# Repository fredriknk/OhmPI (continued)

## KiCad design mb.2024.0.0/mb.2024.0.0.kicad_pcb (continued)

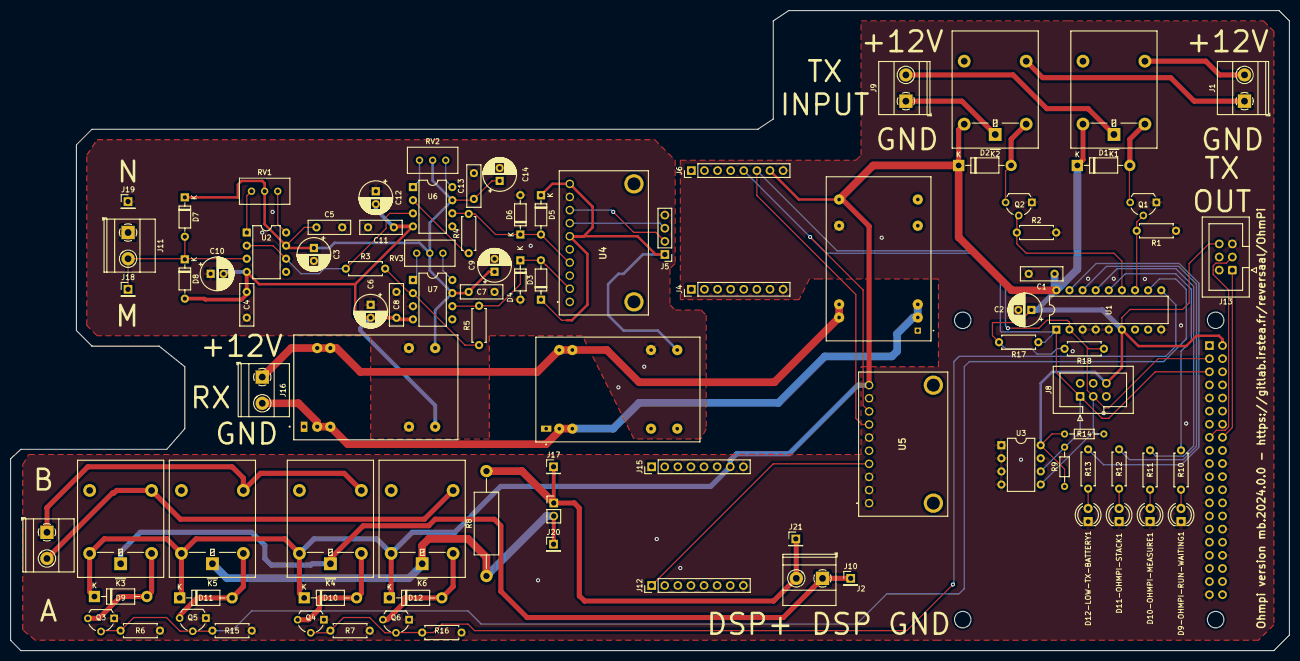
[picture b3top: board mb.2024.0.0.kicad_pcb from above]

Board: 2 copper layers, 247.8 x 124.0 mm, 94 parts (1 on the bottom side), 54 nets.

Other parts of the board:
D7, D8: BAT86; D_DO-35_SOD27_P7.62mm_Horizontal
D9-OHMPI-RUN-WAITING1, D10-OHMPI-MEASURE1, D11-OHMPI-STACK1, D12-LOW-TX-BATTERY1: LED; LED_D4.0mm
R10, R11, R12, R13: 330 ohms; R_Axial_DIN0207_L6.3mm_D2.5mm_P7.62mm_Horizontal

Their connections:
+12V_A: D7.1 (K); also elsewhere on the board
-12V_A: D8.2 (A); also elsewhere on the board
/Vmn_measurement/Electrode_M: D7.2 (A), D8.1 (K); also elsewhere on the board
GNDD: D9-OHMPI-RUN-WAITING1.1 (K), D10-OHMPI-MEASURE1.1 (K), D11-OHMPI-STACK1.1 (K), D12-LOW-TX-BATTERY1.1 (K); also elsewhere on the board
GP4: R10.1; also elsewhere on the board
GP5: R11.1; also elsewhere on the board
GP6: R12.1; also elsewhere on the board
GP7: R13.1; also elsewhere on the board
unnamed: D9-OHMPI-RUN-WAITING1.2 (A), R10.2
unnamed: D10-OHMPI-MEASURE1.2 (A), R11.2
unnamed: D11-OHMPI-STACK1.2 (A), R12.2
unnamed: D12-LOW-TX-BATTERY1.2 (A), R13.2

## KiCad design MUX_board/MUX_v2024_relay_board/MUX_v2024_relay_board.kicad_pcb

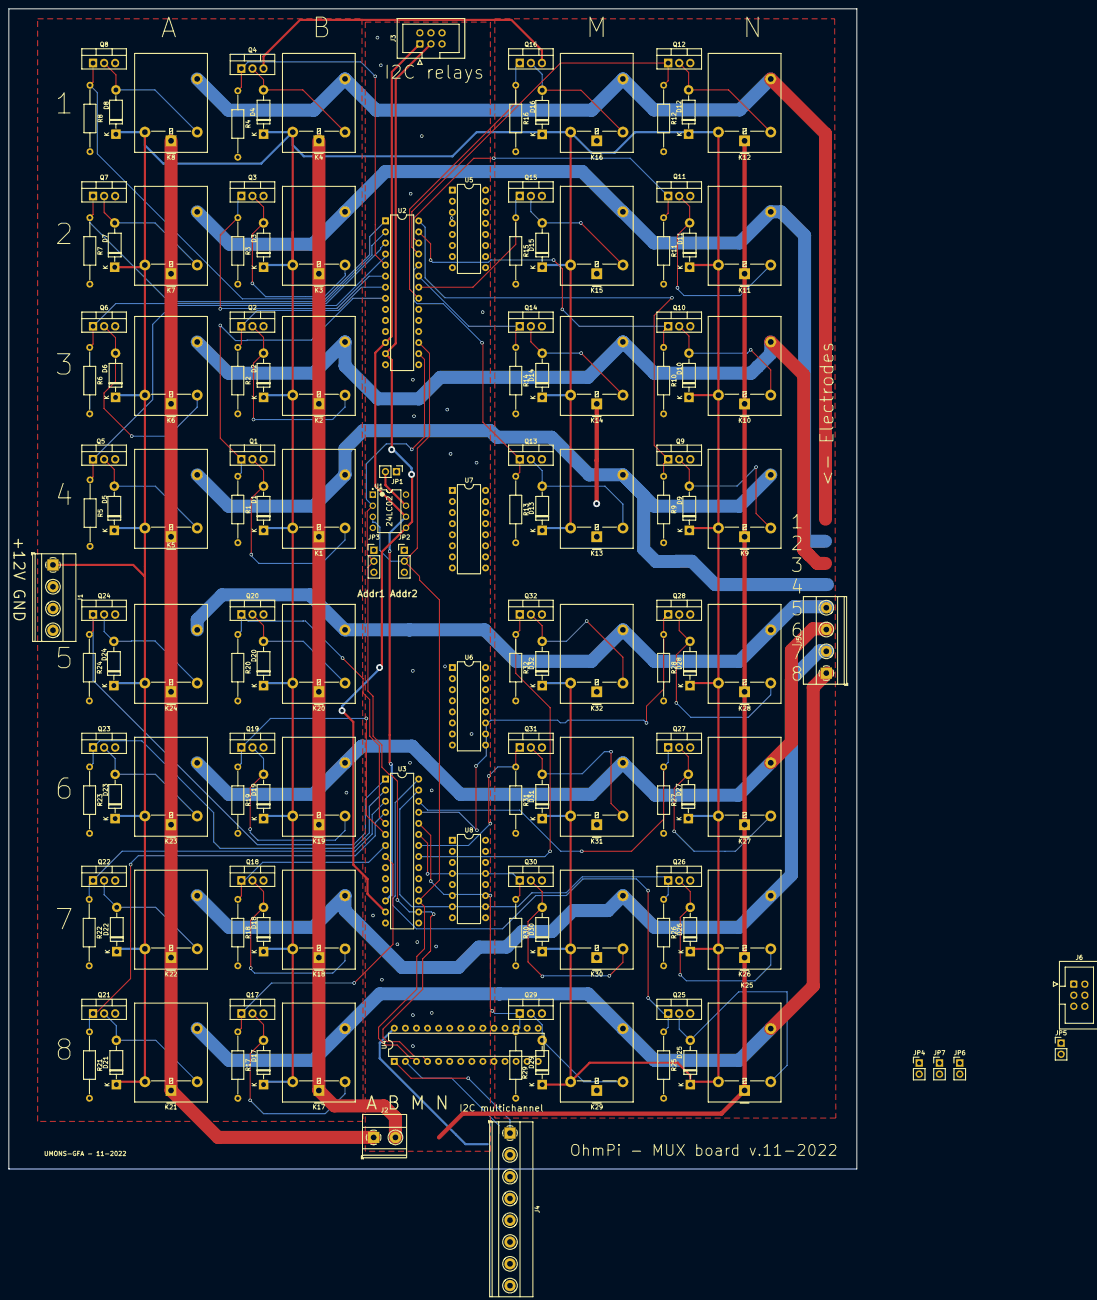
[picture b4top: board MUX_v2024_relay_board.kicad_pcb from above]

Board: 2 copper layers, 194.6 x 266.2 mm, 149 parts (0 on the bottom side), 114 nets.

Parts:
D1, D2, D3, D4, D5, D6, D7, D8, D9, D10, D11, D12, D13, D14, D15, D16, D17, D18, D19, D20, D21, D22, D23, D24, D25, D26, D27, D28, D29, D30, D31, D32: 1N_E4007; D_DO-41_SOD81_P10.16mm_Horizontal
J1, J5: A B M N; TerminalBlock_Phoenix_MKDS-1,5-4_1x04_P5.00mm_Horizontal
J2: Relays Pwr; TerminalBlock_Phoenix_MKDS-1,5-2_1x02_P5.00mm_Horizontal
J3, J6: I2C; IDC-Header_2x03_P2.54mm_Vertical
J4: Screw_Terminal_01x08; TerminalBlock_Phoenix_MKDS-1,5-8_1x08_P5.00mm_Horizontal
JP1: Write_Control; PinHeader_1x02_P2.54mm_Vertical
JP2: Addr 2; PinHeader_1x03_P2.54mm_Vertical
JP3: Addr 1; PinHeader_1x03_P2.54mm_Vertical
JP4, JP5, JP6, JP7: Bypass M; PinHeader_1x02_P2.54mm_Vertical
K1, K2, K3, K4, K5, K6, K7, K8, K9, K10, K11, K12, K13, K14, K15, K16, K17, K18, K19, K20, K21, K22, K23, K24, K25, K26, K27, K28, K29, K30, K31, K32: G5LE-1-VD; Relay_SPDT_Omron-G5LE-1-VD
Q1, Q2, Q3, Q4, Q5, Q6, Q7, Q8, Q9, Q10, Q11, Q12, Q13, Q14, Q15, Q16, Q17, Q18, Q19, Q20, Q21, Q22, Q23, Q24, Q25, Q26, Q27, Q28, Q29, Q30, Q31, Q32: STP16NF06L; TO-220-3_Vertical
R1, R2, R3, R4, R5, R6, R7, R8, R9, R10, R11, R12, R13, R14, R15, R16, R17, R18, R19, R20, R21, R22, R23, R24, R25, R26, R27, R28, R29, R30, R31, R32: 100k; R_Axial_DIN0207_L6.3mm_D2.5mm_P15.24mm_Horizontal
U1: 24LC02; Microchip-24LC02B_P-0
U2, U3, U4: MCP23017_SP; DIP-28_W7.62mm
U5, U6, U7, U8: 4052; DIP-16_W7.62mm

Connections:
12V: D1.1 (K), D2.1 (K), D3.1 (K), D4.1 (K), D5.1 (K), D6.1 (K), D7.1 (K), D8.1 (K), D9.1 (K), D10.1 (K), D11.1 (K), D12.1 (K), D13.1 (K), D14.1 (K), D15.1 (K), D16.1 (K), D17.1 (K), D18.1 (K), D19.1 (K), D20.1 (K), D21.1 (K), D22.1 (K), D23.1 (K), D24.1 (K), D25.1 (K), D26.1 (K), D27.1 (K), D28.1 (K), D29.1 (K), D30.1 (K), D31.1 (K), D32.1 (K), J2.1, K1.5, K2.5, K3.5, K4.5, K5.5, K6.5, K7.5, K8.5, K9.5, K10.5, K11.5, K12.5, K13.5, K14.5, K15.5, K16.5, K17.5, K18.5, K19.5, K20.5, K21.5, K22.5, K23.5, K24.5, K25.5, K26.5, K27.5, K28.5, K29.5, K30.5, K31.5, K32.5
+5V: J3.6, JP2.3 (B), JP3.3 (B), U1.1 (A0), U1.8 (VCC), U2.9 (VDD), U2.15 (A0), U3.9 (VDD), U4.9 (VDD)
+5VA: J6.6, U5.16 (VDD), U6.16 (VDD), U7.16 (VDD), U8.16 (VDD)
-5VA: J6.4, U5.7 (VEE), U6.7 (VEE), U7.7 (VEE), U8.7 (VEE)
A_E1: Q8.1 (G), R8.1, U2.1 (GPB0)
A_E2: Q7.1 (G), R7.1, U2.2 (GPB1)
A_E3: Q6.1 (G), R6.1, U2.3 (GPB2)
A_E4: Q5.1 (G), R5.1, U2.4 (GPB3)
A_E5: Q24.1 (G), R24.1, U3.1 (GPB0)
A_E6: Q23.1 (G), R23.1, U3.2 (GPB1)
A_E7: Q22.1 (G), R22.1, U3.3 (GPB2)
A_E8: Q21.1 (G), R21.1, U3.4 (GPB3)
B_E1: Q4.1 (G), R4.1, U2.5 (GPB4)
B_E2: Q3.1 (G), R3.1, U2.6 (GPB5)
B_E3: Q2.1 (G), R2.1, U2.7 (GPB6)
B_E4: Q1.1 (G), R1.1, U2.8 (GPB7)
B_E5: Q20.1 (G), R20.1, U3.5 (GPB4)
B_E6: Q19.1 (G), R19.1, U3.6 (GPB5)
B_E7: Q18.1 (G), R18.1, U3.7 (GPB6)
B_E8: Q17.1 (G), R17.1, U3.8 (GPB7)
Electrode 1: J4.1, K4.3, K8.3, K12.3, K16.3
Electrode 2: J4.2, K3.3, K7.3, K11.3, K15.3
Electrode 3: J4.3, K2.3, K6.3, K10.3, K14.3
Electrode 4: J4.4, K1.3, K5.3, K9.3, K13.3
Electrode 5: J4.5, K20.3, K24.3, K28.3, K32.3
Electrode 6: J4.6, K19.3, K23.3, K27.3, K31.3
Electrode 7: J4.7, K18.3, K22.3, K26.3, K30.3
Electrode 8: J4.8, K17.3, K21.3, K25.3, K29.3
Enable_MUX1: U4.3 (GPB2), U5.6 (Inh)
Enable_MUX2: U4.7 (GPB6), U7.6 (Inh)
Enable_MUX3: U4.23 (GPA2), U6.6 (Inh)
Enable_MUX4: U4.27 (GPA6), U8.6 (Inh)
GND: J2.2, Q1.3 (S), Q2.3 (S), Q3.3 (S), Q4.3 (S), Q5.3 (S), Q6.3 (S), Q7.3 (S), Q8.3 (S), Q9.3 (S), Q10.3 (S), Q11.3 (S), Q12.3 (S), Q13.3 (S), Q14.3 (S), Q15.3 (S), Q16.3 (S), Q17.3 (S), Q18.3 (S), Q19.3 (S), Q20.3 (S), Q21.3 (S), Q22.3 (S), Q23.3 (S), Q24.3 (S), Q25.3 (S), Q26.3 (S), Q27.3 (S), Q28.3 (S), Q29.3 (S), Q30.3 (S), Q31.3 (S), Q32.3 (S), R1.2, R2.2, R3.2, R4.2, R5.2, R6.2, R7.2, R8.2, R9.2, R10.2, R11.2, R12.2, R13.2, R14.2, R15.2, R16.2, R17.2, R18.2, R19.2, R20.2, R21.2, R22.2, R23.2, R24.2, R25.2, R26.2, R27.2, R28.2, R29.2, R30.2, R31.2, R32.2
GNDA: J6.5, U5.8 (VSS), U6.8 (VSS), U7.8 (VSS), U8.8 (VSS)
GNDD: J3.5, JP1.1 (A), JP2.1 (A), JP3.1 (A), U1.4 (GND), U2.10 (VSS), U3.10 (VSS), U3.15 (A0), U4.10 (VSS), U4.15 (A0)
M_E1: Q16.1 (G), R16.1, U2.21 (GPA0)
M_E2: Q15.1 (G), R15.1, U2.22 (GPA1)
M_E3: Q14.1 (G), R14.1, U2.23 (GPA2)
M_E4: Q13.1 (G), R13.1, U2.24 (GPA3)
M_E5: Q32.1 (G), R32.1, U3.21 (GPA0)
M_E6: Q31.1 (G), R31.1, U3.22 (GPA1)
M_E7: Q30.1 (G), R30.1, U3.23 (GPA2)
M_E8: Q29.1 (G), R29.1, U3.24 (GPA3)
N_E1: Q12.1 (G), R12.1, U2.25 (GPA4)
N_E2: Q11.1 (G), R11.1, U2.26 (GPA5)
N_E3: Q10.1 (G), R10.1, U2.27 (GPA6)
N_E4: Q9.1 (G), R9.1, U2.28 (GPA7)
N_E5: Q28.1 (G), R28.1, U3.25 (GPA4)
N_E6: Q27.1 (G), R27.1, U3.26 (GPA5)
N_E7: Q26.1 (G), R26.1, U3.27 (GPA6)
N_E8: Q25.1 (G), R25.1, U3.28 (GPA7)
unnamed: D1.2 (A), K1.2, Q1.2 (D)
unnamed: D2.2 (A), K2.2, Q2.2 (D)
unnamed: D3.2 (A), K3.2, Q3.2 (D)
unnamed: D4.2 (A), K4.2, Q4.2 (D)
unnamed: D5.2 (A), K5.2, Q5.2 (D)
unnamed: D6.2 (A), K6.2, Q6.2 (D)
unnamed: D7.2 (A), K7.2, Q7.2 (D)
unnamed: D8.2 (A), K8.2, Q8.2 (D)
unnamed: D9.2 (A), K9.2, Q9.2 (D)
unnamed: D10.2 (A), K10.2, Q10.2 (D)
unnamed: D11.2 (A), K11.2, Q11.2 (D)
unnamed: D12.2 (A), K12.2, Q12.2 (D)
unnamed: D13.2 (A), K13.2, Q13.2 (D)
unnamed: D14.2 (A), K14.2, Q14.2 (D)
unnamed: D15.2 (A), K15.2, Q15.2 (D)
unnamed: D16.2 (A), K16.2, Q16.2 (D)
unnamed: D17.2 (A), K17.2, Q17.2 (D)
unnamed: D18.2 (A), K18.2, Q18.2 (D)
unnamed: D19.2 (A), K19.2, Q19.2 (D)
unnamed: D20.2 (A), K20.2, Q20.2 (D)
unnamed: D21.2 (A), K21.2, Q21.2 (D)
unnamed: D22.2 (A), K22.2, Q22.2 (D)
unnamed: D23.2 (A), K23.2, Q23.2 (D)
unnamed: D24.2 (A), K24.2, Q24.2 (D)
unnamed: D25.2 (A), K25.2, Q25.2 (D)
unnamed: D26.2 (A), K26.2, Q26.2 (D)
unnamed: D27.2 (A), K27.2, Q27.2 (D)
unnamed: D28.2 (A), K28.2, Q28.2 (D)
unnamed: D29.2 (A), K29.2, Q29.2 (D)
unnamed: D30.2 (A), K30.2, Q30.2 (D)
unnamed: D31.2 (A), K31.2, Q31.2 (D)
unnamed: D32.2 (A), K32.2, Q32.2 (D)
unnamed: JP1.2 (B), U1.7 (WP)
unnamed: JP2.2 (C), U1.3 (A2), U2.17 (A2), U3.17 (A2), U4.17 (A2)
unnamed: JP3.2 (C), U1.2 (A1), U2.16 (A1), U3.16 (A1), U4.16 (A1)
Role A: J1.1, K5.1, K6.1, K7.1, K8.1, K21.1, K22.1, K23.1, K24.1
Role B: J1.2, K1.1, K2.1, K3.1, K4.1, K17.1, K18.1, K19.1, K20.1
Role M: J1.3, JP4.1 (A), JP5.1 (A), JP6.1 (A), JP7.1 (A)
Role M1: J5.1, JP4.2 (B), JP5.2 (B), JP6.2 (B), JP7.2 (B), U5.1 (Y0), U5.12 (X0), U6.1 (Y0), U6.12 (X0), U7.1 (Y0), U7.12 (X0), U8.1 (Y0), U8.12 (X0)
Role M2: J5.2, U5.5 (Y1), U5.14 (X1), U6.5 (Y1), U6.14 (X1), U7.5 (Y1), U7.14 (X1), U8.5 (Y1), U8.14 (X1)
Role M3: U5.2 (Y2), U5.15 (X2), U6.2 (Y2), U6.15 (X2), U7.2 (Y2), U7.15 (X2), U8.2 (Y2), U8.15 (X2)
Role M4: J5.3, J5.4, U5.4 (Y3), U5.11 (X3), U6.4 (Y3), U6.11 (X3), U7.4 (Y3), U7.11 (X3), U8.4 (Y3), U8.11 (X3)
Role M_E1: K16.1, U5.13 (X)
Role M_E2: K15.1, U5.3 (Y)
Role M_E3: K14.1, U7.13 (X)
Role M_E4: K13.1, U7.3 (Y)
Role M_E5: K32.1, U6.13 (X)
Role M_E6: K31.1, U6.3 (Y)
Role M_E7: K30.1, U8.13 (X)
Role M_E8: K29.1, U8.3 (Y)
Role N: J1.4, K9.1, K10.1, K11.1, K12.1, K25.1, K26.1, K27.1, K28.1
S1_MUX1: U4.1 (GPB0), U5.10 (A)
S1_MUX2: U4.5 (GPB4), U7.10 (A)
S1_MUX3: U4.21 (GPA0), U6.10 (A)
S1_MUX4: U4.25 (GPA4), U8.10 (A)
S2_MUX1: U4.2 (GPB1), U5.9 (B)
S2_MUX2: U4.6 (GPB5), U7.9 (B)
S2_MUX3: U4.22 (GPA1), U6.9 (B)
S2_MUX4: U4.26 (GPA5), U8.9 (B)
SCL1: J3.1, U1.6 (SCL), U2.12 (SCK), U3.12 (SCK)
SCL2: J6.1, U4.12 (SCK)
SDA_1: J3.3, U1.5 (SDA), U2.13 (SDA), U3.13 (SDA)
SDA_2: J6.3, U4.13 (SDA)

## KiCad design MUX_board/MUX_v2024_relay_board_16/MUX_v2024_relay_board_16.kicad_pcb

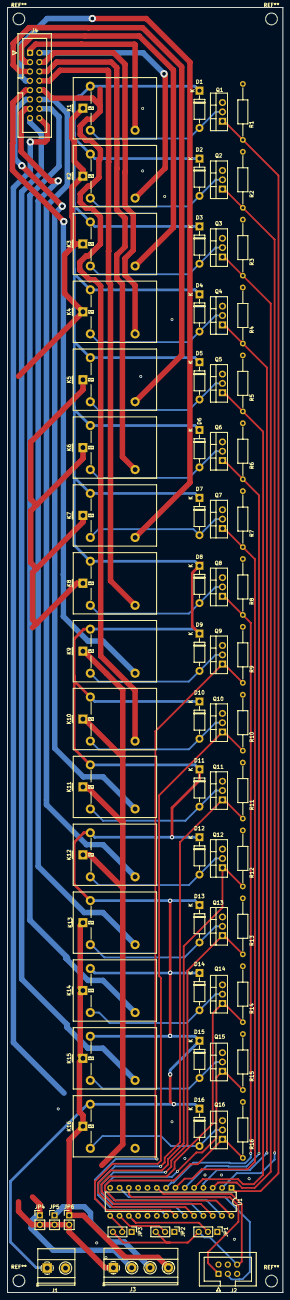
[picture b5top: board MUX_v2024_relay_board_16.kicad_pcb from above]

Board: 2 copper layers, 75.0 x 350.0 mm, 75 parts (0 on the bottom side), 60 nets.

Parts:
D1, D2, D3, D4, D5, D6, D7, D8, D9, D10, D11, D12, D13, D14, D15, D16: 1N_E4007; D_DO-41_SOD81_P10.16mm_Horizontal
J1: Relays Pwr; TerminalBlock_Phoenix_MKDS-1,5-2_1x02_P5.00mm_Horizontal
J2: I2C; IDC-Header_2x03_P2.54mm_Vertical
J3: Screw_Terminal_01x04; TerminalBlock_Phoenix_MKDS-1,5-4_1x04_P5.00mm_Horizontal
J4: Conn_02x08_Odd_Even; IDC-Header_2x08_P2.54mm_Vertical
JP1: Addr 2; PinHeader_1x03_P2.54mm_Vertical
JP2: Addr 1; PinHeader_1x03_P2.54mm_Vertical
JP3: Addr 0; PinHeader_1x03_P2.54mm_Vertical
JP4, JP5, JP6: Jumper_2_Open; PinHeader_1x02_P2.54mm_Vertical
K1, K2, K3, K4, K5, K6, K7, K8, K9, K10, K11, K12, K13, K14, K15, K16: G5LE-1-VD; Relay_SPDT_Omron-G5LE-1-VD
Q1, Q2, Q3, Q4, Q5, Q6, Q7, Q8, Q9, Q10, Q11, Q12, Q13, Q14, Q15, Q16: STP16NF06L; TO-220-3_Vertical
R1, R2, R3, R4, R5, R6, R7, R8, R9, R10, R11, R12, R13, R14, R15, R16: 100k; R_Axial_DIN0207_L6.3mm_D2.5mm_P15.24mm_Horizontal
U1: MCP23017_SP; DIP-28_W7.62mm

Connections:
12V: D1.1 (K), D2.1 (K), D3.1 (K), D4.1 (K), D5.1 (K), D6.1 (K), D7.1 (K), D8.1 (K), D9.1 (K), D10.1 (K), D11.1 (K), D12.1 (K), D13.1 (K), D14.1 (K), D15.1 (K), D16.1 (K), J1.1, K1.5, K2.5, K3.5, K4.5, K5.5, K6.5, K7.5, K8.5, K9.5, K10.5, K11.5, K12.5, K13.5, K14.5, K15.5, K16.5
+5V: J2.6, JP1.3 (B), JP2.3 (B), JP3.3 (B), U1.9 (VDD)
Addr0: JP3.2 (C), U1.15 (A0)
Addr1: JP2.2 (C), U1.16 (A1)
Addr2: JP1.2 (C), U1.17 (A2)
E1: Q1.1 (G), R1.1, U1.1 (GPB0)
E2: Q2.1 (G), R2.1, U1.2 (GPB1)
E3: Q3.1 (G), R3.1, U1.3 (GPB2)
E4: Q4.1 (G), R4.1, U1.4 (GPB3)
E5: Q5.1 (G), R5.1, U1.5 (GPB4)
E6: Q6.1 (G), R6.1, U1.6 (GPB5)
E7: Q7.1 (G), R7.1, U1.7 (GPB6)
E8: Q8.1 (G), R8.1, U1.8 (GPB7)
E9: Q9.1 (G), R9.1, U1.21 (GPA0)
E10: Q10.1 (G), R10.1, U1.22 (GPA1)
E11: Q11.1 (G), R11.1, U1.23 (GPA2)
E12: Q12.1 (G), R12.1, U1.24 (GPA3)
E13: Q13.1 (G), R13.1, U1.25 (GPA4)
E14: Q14.1 (G), R14.1, U1.26 (GPA5)
E15: Q15.1 (G), R15.1, U1.27 (GPA6)
E16: Q16.1 (G), R16.1, U1.28 (GPA7)
Electrode 1: J4.1, K1.3
Electrode 2: J4.2, K2.3
Electrode 3: J4.3, K3.3
Electrode 4: J4.4, K4.3
Electrode 5: J4.5, K5.3
Electrode 6: J4.6, K6.3
Electrode 7: J4.7, K7.3
Electrode 8: J4.8, K8.3
Electrode 9: J4.9, K9.3
Electrode 10: J4.10, K10.3
Electrode 11: J4.11, K11.3
Electrode 12: J4.12, K12.3
Electrode 13: J4.13, K13.3
Electrode 14: J4.14, K14.3
Electrode 15: J4.15, K15.3
Electrode 16: J4.16, K16.3
GND: J1.2, J2.5, JP1.1 (A), JP2.1 (A), JP3.1 (A), Q1.3 (S), Q2.3 (S), Q3.3 (S), Q4.3 (S), Q5.3 (S), Q6.3 (S), Q7.3 (S), Q8.3 (S), Q9.3 (S), Q10.3 (S), Q11.3 (S), Q12.3 (S), Q13.3 (S), Q14.3 (S), Q15.3 (S), Q16.3 (S), R1.2, R2.2, R3.2, R4.2, R5.2, R6.2, R7.2, R8.2, R9.2, R10.2, R11.2, R12.2, R13.2, R14.2, R15.2, R16.2, U1.10 (VSS)
unnamed: D1.2 (A), K1.2, Q1.2 (D)
unnamed: D2.2 (A), K2.2, Q2.2 (D)
unnamed: D3.2 (A), K3.2, Q3.2 (D)
unnamed: D4.2 (A), K4.2, Q4.2 (D)
unnamed: D5.2 (A), K5.2, Q5.2 (D)
unnamed: D6.2 (A), K6.2, Q6.2 (D)
unnamed: D7.2 (A), K7.2, Q7.2 (D)
unnamed: D8.2 (A), K8.2, Q8.2 (D)
unnamed: D9.2 (A), K9.2, Q9.2 (D)
unnamed: D10.2 (A), K10.2, Q10.2 (D)
unnamed: D11.2 (A), K11.2, Q11.2 (D)
unnamed: D12.2 (A), K12.2, Q12.2 (D)
unnamed: D13.2 (A), K13.2, Q13.2 (D)
unnamed: D14.2 (A), K14.2, Q14.2 (D)
unnamed: D15.2 (A), K15.2, Q15.2 (D)
unnamed: D16.2 (A), K16.2, Q16.2 (D)
Role A: J3.1, JP4.2 (B), JP5.2 (B), JP6.2 (B), K1.1, K2.1, K3.1, K4.1
Role B: J3.2, JP4.1 (A), K5.1, K6.1, K7.1, K8.1
Role M: J3.3, JP5.1 (A), K9.1, K10.1, K11.1, K12.1
Role N: J3.4, JP6.1 (A), K13.1, K14.1, K15.1, K16.1
SCL1: J2.1, U1.12 (SCK)
SD1: J2.3, U1.13 (SDA)

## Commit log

2020-12-27 modification du fichier ABMN
2022-11-21 Adds draft kicad schematics for MUX boards for 8 electrodes with ABMN roles. It includes 4:1 multiplexing on M roles for multichannel acquisition.
2022-11-21 Updates and rename MUX_v2024_relay_board
2022-11-21 Renames MUX_v2024_relay_board
2022-11-24 Modifies schematics for scenario with single MN relays and analog multiplexers for roles M1 M2 and N. This assumes that the measurement board is modified to allow simultaneous measurements of M1 and 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
2022-11-29 Adds dummy function in utils to measure battery
2022-12-08 Adds a WEMOS D1 mini script for handling switching between battery recharge and battery use as well as battery potential measurement
2022-12-10 Adds a shutdown command...
2022-12-13 Issue #93 adds a check on the battery level
2022-12-14 Updates relay board to versatile 32 relays board addressing 16 electrodes and 2 roles or 8 electrodes and 4 roles
2022-12-14 Updates MUX relay board
2022-12-15 Fixes last errors on pcb
2022-12-16 Improves annotations on pcb board
2023-02-14 Adds MUX addressing tables
2023-02-14 Refactor directory MUX board 2024.0.0
2023-02-14 Refactors MUX board 2024.0.0
2023-02-14 Fixes merge conflicts
2023-02-14 Updates mux v2024 addressing
2023-02-14 Adds MUX board 2024 capability
2023-02-15 improves mux addressing and adds switch_mux_quad function
2023-03-09 Updates footprints
2023-04-05 Adds pull up on MCP
2023-04-06 Adds capacitor on MCP
2023-04-07 Fixes autogain False/True conditions
2023-04-07 Adds duty cycle in run_measurement to shorten no-injection duration if needed
2023-04-10 proposed refactoring with hw.py and sw.py (see hwTest.py for offpi simulation) #98
2023-04-10 Revert "proposed refactoring with hw.py and sw.py (see hwTest.py for offpi simulation) #98"
    This reverts commit 559ef01216c33302ed2da5494b10ee064ee2fe51
2023-04-15 update test_mux function and fix some bugs
2023-04-19 improves duty_cycle
2023-04-19 Adds plots module and plot_realtime_fulldata capability in run_sequence
2023-04-23 Correction of the continuous mode, for a good measurement.
2023-04-26 adds ohmpi_ML
2023-04-26 adds notebook
2023-04-26 update measurement board schematics and circuit
2023-05-02 adds filtering capacitors on MCP23017
2023-05-03 imrpoves labelling
2023-05-03 Improves TCA board PCB design
2023-05-10 update pcb
2023-06-02 update ohmpi with ohmpi_ml
2023-06-02 update continuis mode
2023-06-02 change run_measurement_new to run_measurment
2023-06-02 ajust time after dps run
2023-06-02 update time
2023-06-02 deacrese time sampling for IP
2023-06-06 correction of ads continious mode inversion between current and voltage
2023-06-06 max current allow
2023-06-07 adds second I2C bus capability for mux and fix bugs
2023-06-07 fixes plot in realtime
2023-06-07 Adds second i2c bus capability
2023-06-07 fixes plots in real_time
2023-06-07 update last version with nex examples
2023-06-07 fixes plots
2023-06-07 add test_led function
2023-06-07 Adds vmn_offset
2023-06-07 Adds battery_level readings
2023-06-07 Adds Pab and Vab
2023-06-07 Fixes RS_check
2023-06-07 Fixes rs_check and export dir and name
2023-06-07 remove ohmpi_ml
2023-06-07 Adds rs_check example
2023-06-07 new function export to bert
2023-06-07 Fixes vmax strategy
2023-06-07 Fixes injection strategies
2023-06-07 Fixes rs check issue from merge
2023-06-08 adds sampling_interval as a settings
2023-06-08 Fixes sampling interval strategy (minimum sampling interval when reading u0 and u2 is 10 ms)
2023-06-13 issue #109 : add U0 and U2 factors
2023-06-13 issue # 109: now we added an offset
2023-06-13 a first attempt to measure M... to be tested!!
